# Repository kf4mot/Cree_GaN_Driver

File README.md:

# Cree GaN Gate Driver and Power Sequencer.
A general purpose GaN gate driver board based on [Cree APPNOTE-011 Rev. B](https://github.com/kf4mot/Cree_GaN_Driver/blob/master/docs/gan_hemt_biasing_circuit_with_temperature_compensation.pdf).
Provides about 2 ms of delay after power is good before switching on the mosfet. Switch off during power fail or shut down is nearly instant.

**Incomplete. Tested with DC load for function and power sequencing only.**

**Things worth knowing**

1. If operating at 14 Volts or less then R10 should be decreased from 4.7KΩ to 1KΩ.
1. C8 value can change per installation, or is optional. A though hole electrolytic soldered to the adjacent power pads is also a convenient option for bulk capacitance.
1. Infineon SPD15P10PL G can be used as a alternate mosfet. **Untested**
1. The series resistance that is R11, R13, and RV1 is there for hackability. Allowing for GaN's with differing gate voltage requirements and to have the ability to use fixed resistors for preventing voltage shift.

[Schematic](https://github.com/kf4mot/Cree_GaN_Driver/blob/master/hardware/Cree_GaN_Driver.pdf)

[Licensed under CERN-OHL-S V2. Julian White, 2020](https://www.ohwr.org/project/cernohl/wikis/home)

Ch.1 is drain. Ch.2 is gate.

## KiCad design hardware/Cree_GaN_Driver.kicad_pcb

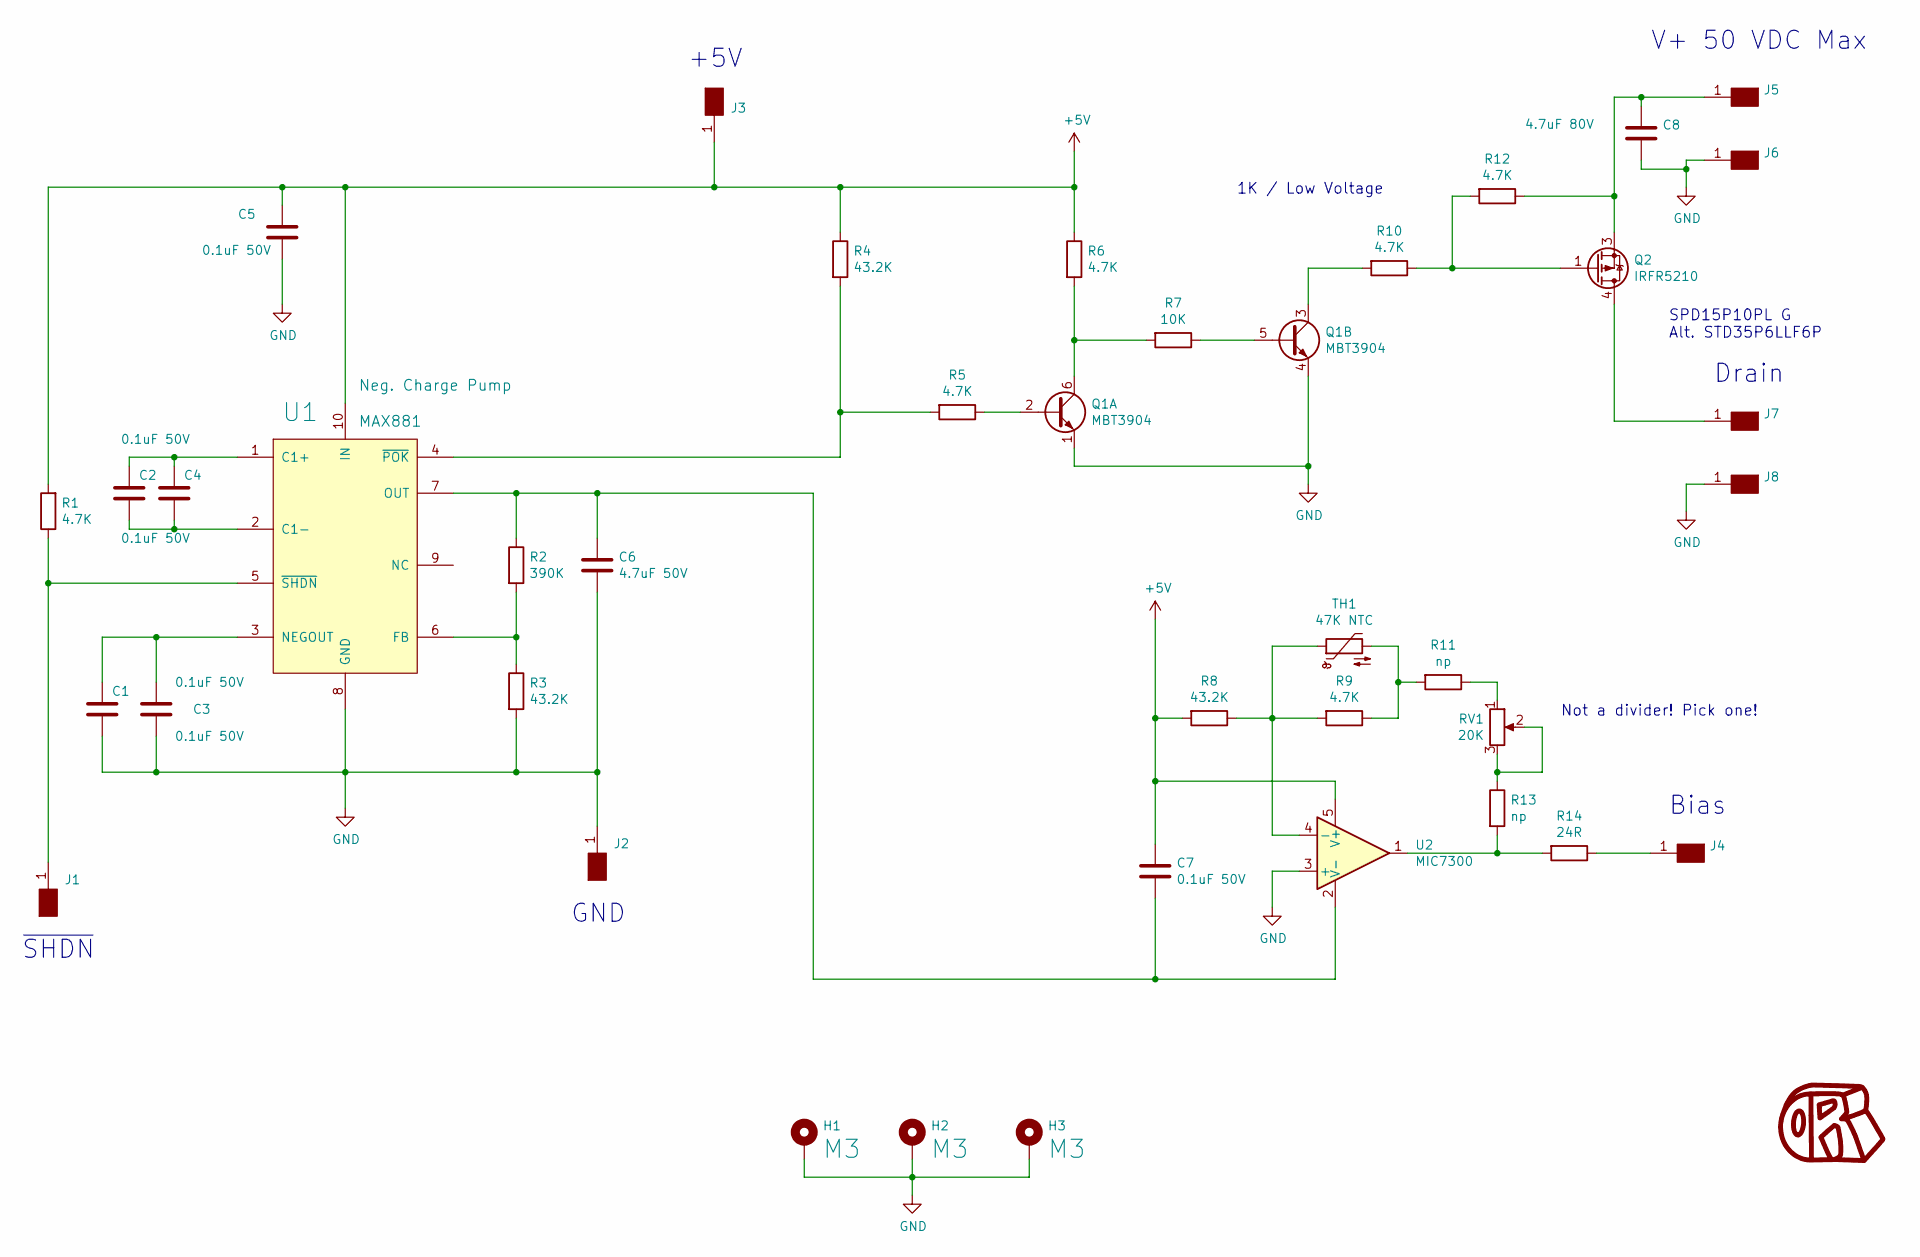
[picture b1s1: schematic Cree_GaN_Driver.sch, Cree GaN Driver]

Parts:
C1, C2, C3, C4, C5, C7: 0.1uF_50V_0805_x7r; C_0805_HandSoldering; Part Number C0805C104K5RACTU
C6: C_4.7uf_50V_x7r_1206; C_1206; Part Number GRM31CR71H475KA12L
C8: 4.7uf_80V_1210; R_1210; Part Number GRM32ER71K475KE14L
H1, H2, H3: MountingHole_Pad_M3; MountingHole_3.2mm_M3_Pad
J1, J2, J3, J4, J5, J6, J7, J8: Conn_5x10mm_pad; SolderWirePad_single_SMD_5x10mm
Q1: MBT3904; SOT-363_SC-70-6; Part Number MBT3904DW1T1G
Q2: IRFR5210; TO-252-3_TabPin4; Part Number IRF5210STRLPBF
R1, R5, R6, R9, R10, R12: R_4.7k_sm0805; R_0805_HandSoldering; Part Number RC0805FR-074K7L
R2: R_390k_sm0603; R_0603; Part Number RT0603FRE07390KL
R3, R4, R8: R_43.2K_sm0805; R_0805_HandSoldering; Part Number RC0805FR-0743K2L
R7: R_10k_sm0603; R_0603; Part Number RT0603FRE0710KL
R11, R13: R; R_0805_HandSoldering; Part Number np
R14: R_24_sm1206; R_1206_HandSoldering; Part Number CR1206-FX-24R0ELF
RV1: R_POT_20K_84WR20KLFTR; POT_TT84W; Part Number 84WR20KLF
TH1: Thermistor_NTC_ERT-J1VV473J; R_0603_HandSoldering; Part Number ERT-J1VV473J
U1: MAX881; MSOP-10_3x3mm_Pitch0.5mm; Part Number MAX881REUB
U2: MIC7300; SOT-23-5; Part Number MIC7300YM5-TR

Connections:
+5V: C5.1, C7.1, J3.1, R1.2, R4.1, R6.1, R8.2, U1.10 (IN), U2.5 (V+)
GND: C1.2, C3.2, C5.2, C6.2, C8.2, H1.1, H2.1, H3.1, J2.1, J6.1, J8.1, Q1.1 (E1), Q1.4 (E1), R3.2, U1.8 (GND), U2.3 (+)
unnamed: C1.1, C3.1, U1.3 (NEGOUT)
unnamed: C2.1, C4.1, U1.1 (C1+)
unnamed: C2.2, C4.2, U1.2 (C1-)
unnamed: C6.1, C7.2, R2.1, U1.7 (OUT), U2.2 (V-)
unnamed: C8.1, J5.1, Q2.3 (S), R12.1
unnamed: J1.1, R1.1, U1.5 (~SHDN)
unnamed: J4.1, R14.1
unnamed: J7.1, Q2.4 (D)
unnamed: Q1.2 (B1), R5.1
unnamed: Q1.3 (C1), R10.2
unnamed: Q1.5 (B1), R7.1
unnamed: Q1.6 (C1), R6.2, R7.2
unnamed: Q2.1 (G), R10.1, R12.2
unnamed: R2.2, R3.1, U1.6 (FB)
unnamed: R4.2, R5.2, U1.4 (~POK)
unnamed: R8.1, R9.2, TH1.1, U2.4 (-)
unnamed: R11.1, RV1.1
unnamed: R9.1, R11.2, TH1.2
unnamed: R13.1, RV1.2, RV1.3
unnamed: R13.2, R14.2, U2.1

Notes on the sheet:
~SHDN
+5V
V+ 50 VDC Max
Drain
Bias
GND
SPD15P10PL G Alt. STD35P6LLF6P
1K / Low Voltage
Not a divider! Pick one!

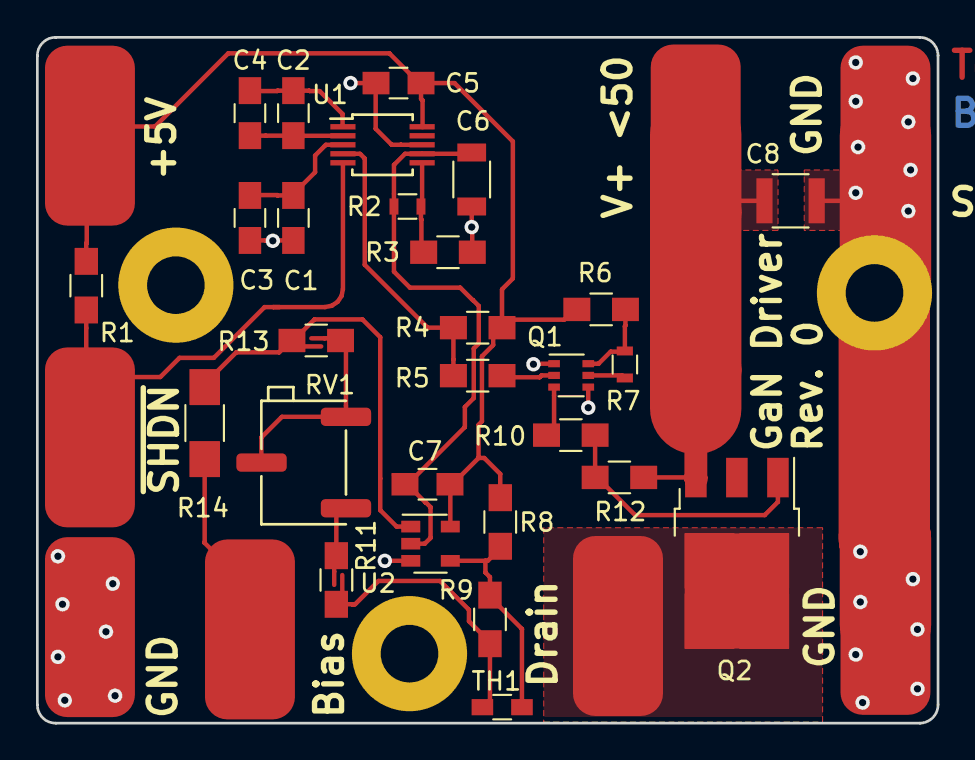
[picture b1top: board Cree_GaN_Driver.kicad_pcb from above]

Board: 2 copper layers, 50.0 x 38.1 mm, 39 parts (0 on the bottom side), 22 nets.
